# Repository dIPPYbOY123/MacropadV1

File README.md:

# MacropadV1

MacropadV1 is a custom-designed 6-key mechanical macropad featuring a rotary encoder, an OLED display, and RGB lighting. It's powered by the Seeed Xiao RP2040 and running KMK firmware.

## Features

- **6 Mechanical Switches**: MX-style switches.
- **Rotary Encoder**: Smooth scrolling and volume control.
- **OLED Display (128x32)**: Real-time feedback on layers, status, and custom animations.
- **7 Addressable RGB LEDs**: Fully customizable underglow and per-key lighting.
- **Compact Design**: Custom-designed 3D printable case for minimalistic vibe.
- **KMK Firmware**: Easily customizable using Python.

## Bill of Materials (BOM)

| Component | Quantity | Specification |
| :--- | :---: | :--- |
| **Microcontroller** | 1 | Seeed Xiao RP2040 |
| **Switches** | 6 | MX-style Mechanical Switches |
| **Keycaps** | 6 | MX-compatible Keycaps |
| **Rotary Encoder** | 1 | EC11 Encoder with Push Button |
| **OLED Display** | 1 | 0.91" 128x32 I2C OLED |
| **Diodes** | 6 | 1N4148 Through-hole Diodes |
| **RGB LEDs** | 7 | SK6812 Mini-E |
| **PCB** | 1 | Custom MacropadV1 PCB |
| **Hardware** | 4 | M3 x 16mm Screws |
| **Case** | 1 | 3D Printed Case |

### Case Design
Designed in Autodesk Fusion, the project includes a custom 3D printable case designed for a sleek, low-profile look.

| Case Angled View | Case Back View |
| :---: | :---: |
|  |  |

## Firmware

MacropadV1 runs on **KMK Firmware**, a feature-rich keyboard firmware written in CircuitPython.

### Keymap Configuration
The default keymap includes dedicated layers for media control, macros (Copy/Paste/Save), and RGB lighting effects.

- **Layer 0**: Media controls, Copy/Paste/Cut macros, Screen Snipping.
- **Layer 1**: Navigation and Select All macros.
- **Layer 2**: RGB Lighting controls (Mode, Brightness, Color).

The rotary encoder is mapped to volume control by default.

## PCB & Electronics

The PCB has been designed in KiCad.

### PCB Layout

### 3D Visualizations
| Front | Back |
| :---: | :---: |
|  |  |

### Schematic

## Project Structure

- `firmware/`: KMK configuration (`main.py`)
- `pcb/`: KiCad project files
- `cad/`: 3D design files for the case (STLs/Step)
- `media/`: Project images and documentation assets

---
Designed by **Dip Khadka**

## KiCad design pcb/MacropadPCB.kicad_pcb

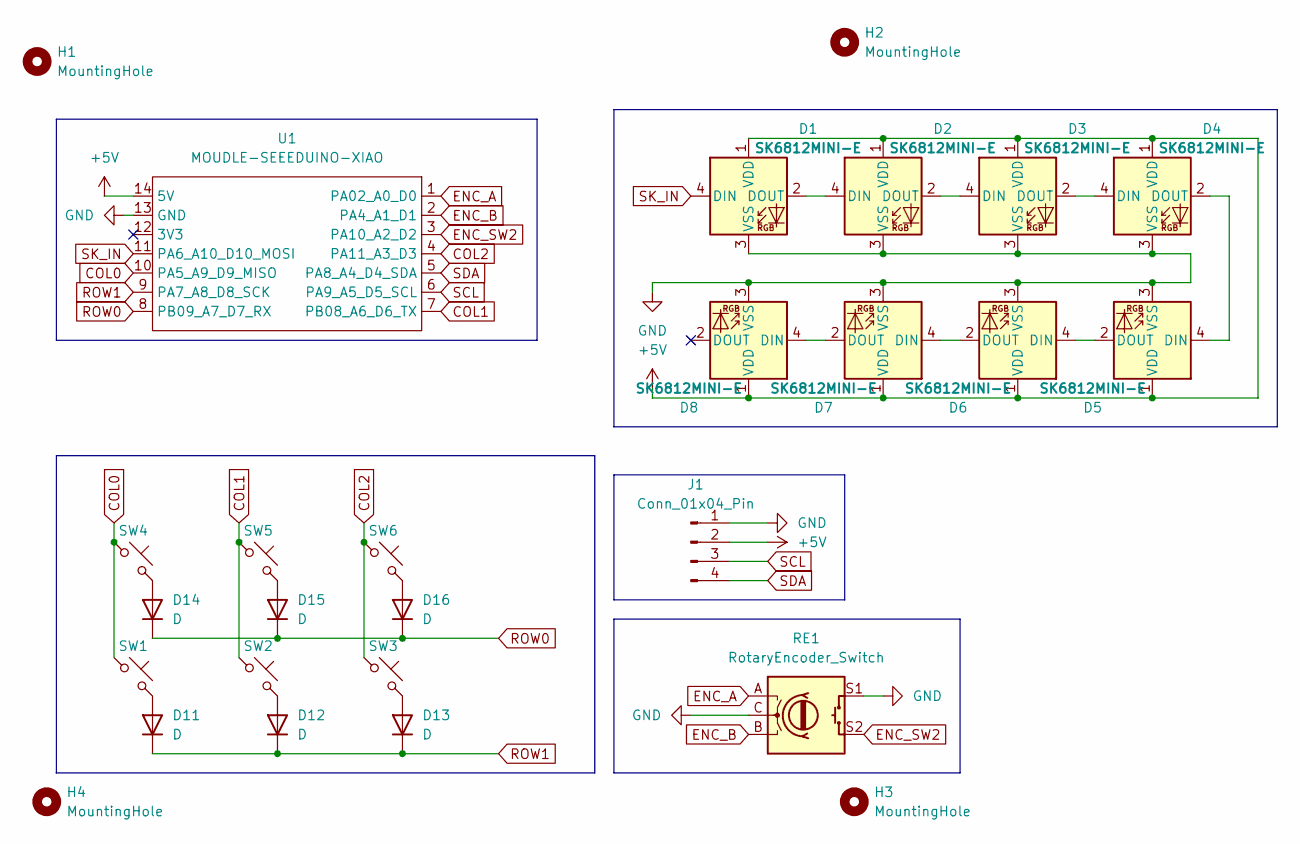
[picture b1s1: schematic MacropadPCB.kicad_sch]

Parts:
D1, D2, D3, D4, D5, D6, D7, D8: SK6812MINI-E; MX_SK6812MINI-E_REV
D11, D12, D13, D14, D15, D16: D; D_DO-35_SOD27_P7.62mm_Horizontal
H1, H2, H3, H4: MountingHole; MountingHole_3.2mm_M3
J1: Conn_01x04_Pin; SSD1306-0.91-OLED-4pin-128x32
RE1: RotaryEncoder_Switch; RotaryEncoder_Alps_EC11E-Switch_Vertical_H20mm
SW1, SW2, SW3, SW4, SW5, SW6: SW_Push_45deg; SW_Cherry_MX_1.00u_PCB
U1: MOUDLE-SEEEDUINO-XIAO; XIAO-Generic-Hybrid-14P-2.54-21X17.8MM

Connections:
+5V: D1.1 (VDD), D2.1 (VDD), D3.1 (VDD), D4.1 (VDD), D5.1 (VDD), D6.1 (VDD), D7.1 (VDD), D8.1 (VDD), J1.2, U1.14 (5V)
COL0: SW1.1, SW4.1, U1.10 (PA5_A9_D9_MISO)
COL1: SW2.1, SW5.1, U1.7 (PB08_A6_D6_TX)
COL2: SW3.1, SW6.1, U1.4 (PA11_A3_D3)
ENC_A: RE1.A, U1.1 (PA02_A0_D0)
ENC_B: RE1.B, U1.2 (PA4_A1_D1)
ENC_SW2: RE1.S2, U1.3 (PA10_A2_D2)
GND: D1.3 (VSS), D2.3 (VSS), D3.3 (VSS), D4.3 (VSS), D5.3 (VSS), D6.3 (VSS), D7.3 (VSS), D8.3 (VSS), J1.1, RE1.C, RE1.S1, U1.13 (GND)
unnamed: D1.2 (DOUT), D2.4 (DIN)
unnamed: D2.2 (DOUT), D3.4 (DIN)
unnamed: D3.2 (DOUT), D4.4 (DIN)
unnamed: D4.2 (DOUT), D5.4 (DIN)
unnamed: D5.2 (DOUT), D6.4 (DIN)
unnamed: D6.2 (DOUT), D7.4 (DIN)
unnamed: D7.2 (DOUT), D8.4 (DIN)
unnamed: D11.2 (A), SW1.2
unnamed: D12.2 (A), SW2.2
unnamed: D13.2 (A), SW3.2
unnamed: D14.2 (A), SW4.2
unnamed: D15.2 (A), SW5.2
unnamed: D16.2 (A), SW6.2
ROW0: D14.1 (K), D15.1 (K), D16.1 (K), U1.8 (PB09_A7_D7_RX)
ROW1: D11.1 (K), D12.1 (K), D13.1 (K), U1.9 (PA7_A8_D8_SCK)
SCL: J1.3, U1.6 (PA9_A5_D5_SCL)
SDA: J1.4, U1.5 (PA8_A4_D4_SDA)
SK_IN: D1.4 (DIN), U1.11 (PA6_A10_D10_MOSI)

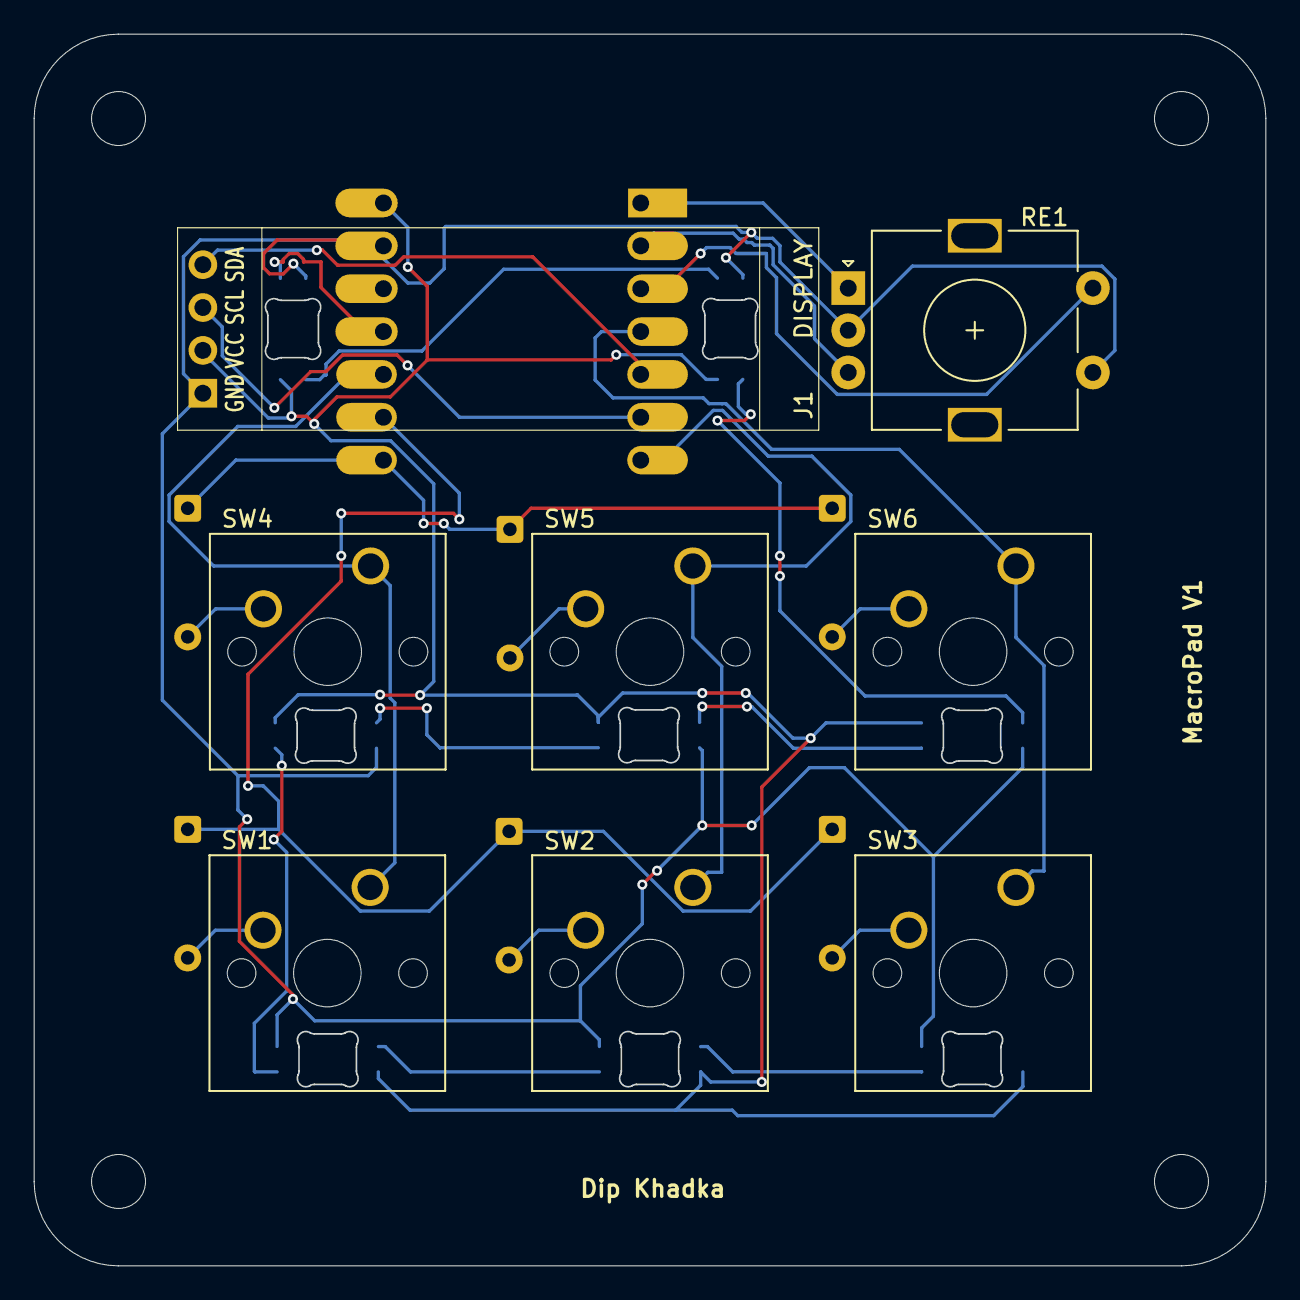
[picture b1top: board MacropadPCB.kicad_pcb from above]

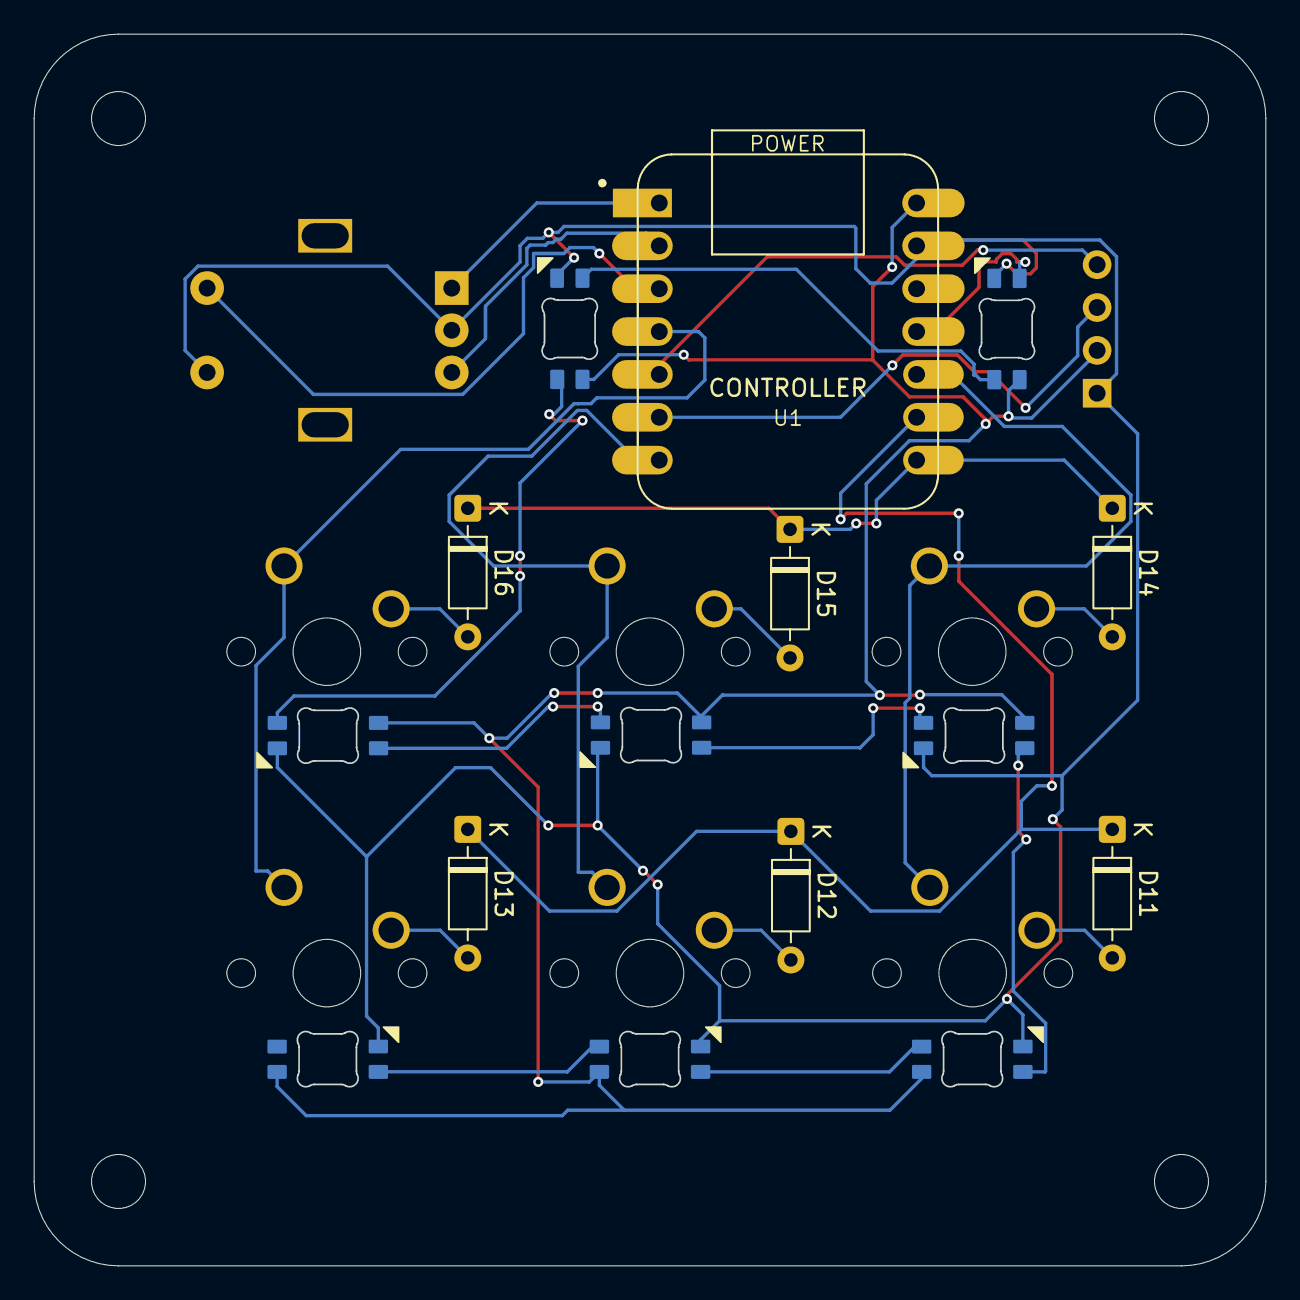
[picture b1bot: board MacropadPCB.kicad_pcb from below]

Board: 2 copper layers, 73.0 x 73.0 mm, 27 parts (7 on the bottom side), 26 nets.

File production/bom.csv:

Designator,Footprint,Quantity,Value,LCSC Part #
"D1, D2, D3, D4, D5, D6, D7, D8",MX_SK6812MINI-E_REV,8,SK6812MINI-E,
"D11, D12, D13, D14, D15, D16",D_DO-35_SOD27_P7.62mm_Horizontal,6,D,
J1,SSD1306-0.91-OLED-4pin-128x32,1,Conn_01x04_Pin,
RE1,RotaryEncoder_Alps_EC11E-Switch_Vertical_H20mm,1,RotaryEncoder_Switch,
"SW1, SW2, SW3, SW4, SW5, SW6",SW_Cherry_MX_1.00u_PCB,6,SW_Push_45deg,
U1,XIAO-Generic-Hybrid-14P-2.54-21X17.8MM,1,MOUDLE-SEEEDUINO-XIAO,

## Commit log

2026-03-10 Initial commit with README and project files
2026-03-10 Updated README images and finalized documentation
2026-03-10 Updated firmware pinouts per user specs
2026-03-10 Sync manual documentation improvements
2026-03-10 Implement OLED Multi-View system with STATUS, MACROS and ABOUT apps
2026-03-10 Update README with RP2040 controller and revised descriptions
2026-03-10 Add detailed Bill of Materials to README
2026-03-10 Finalize BOM: remove cable, update screw size and case description
2026-03-10 Update project images and final documentation refinements
2026-03-10 Update README to use new 3D PCB image filenames
2026-03-10 Remove unwanted screenshot and sync final changes
2026-03-11 Refactor README section headers
    Updated section headers for consistency and removed emojis.
2026-03-11 Fix punctuation and enhance case design description
    Added a period to the end of a sentence and clarified the case design description.
